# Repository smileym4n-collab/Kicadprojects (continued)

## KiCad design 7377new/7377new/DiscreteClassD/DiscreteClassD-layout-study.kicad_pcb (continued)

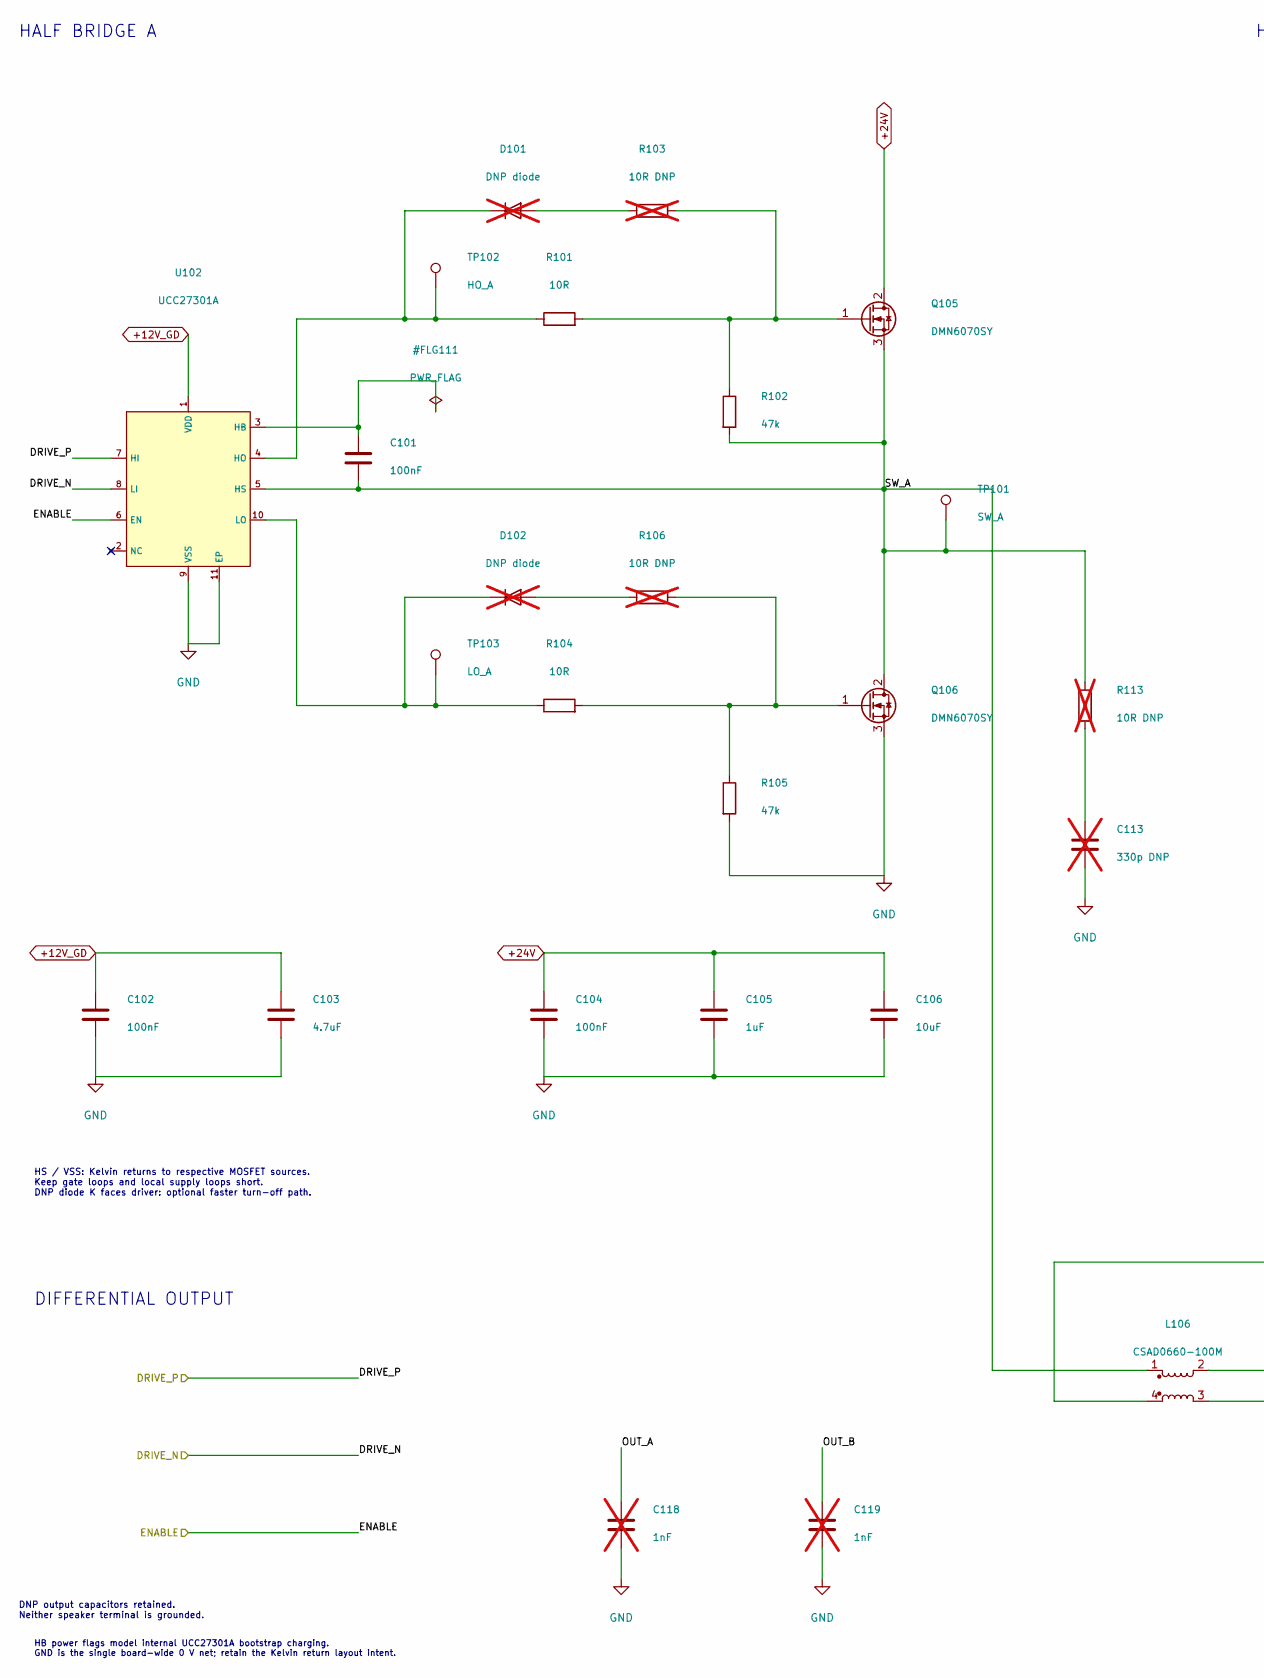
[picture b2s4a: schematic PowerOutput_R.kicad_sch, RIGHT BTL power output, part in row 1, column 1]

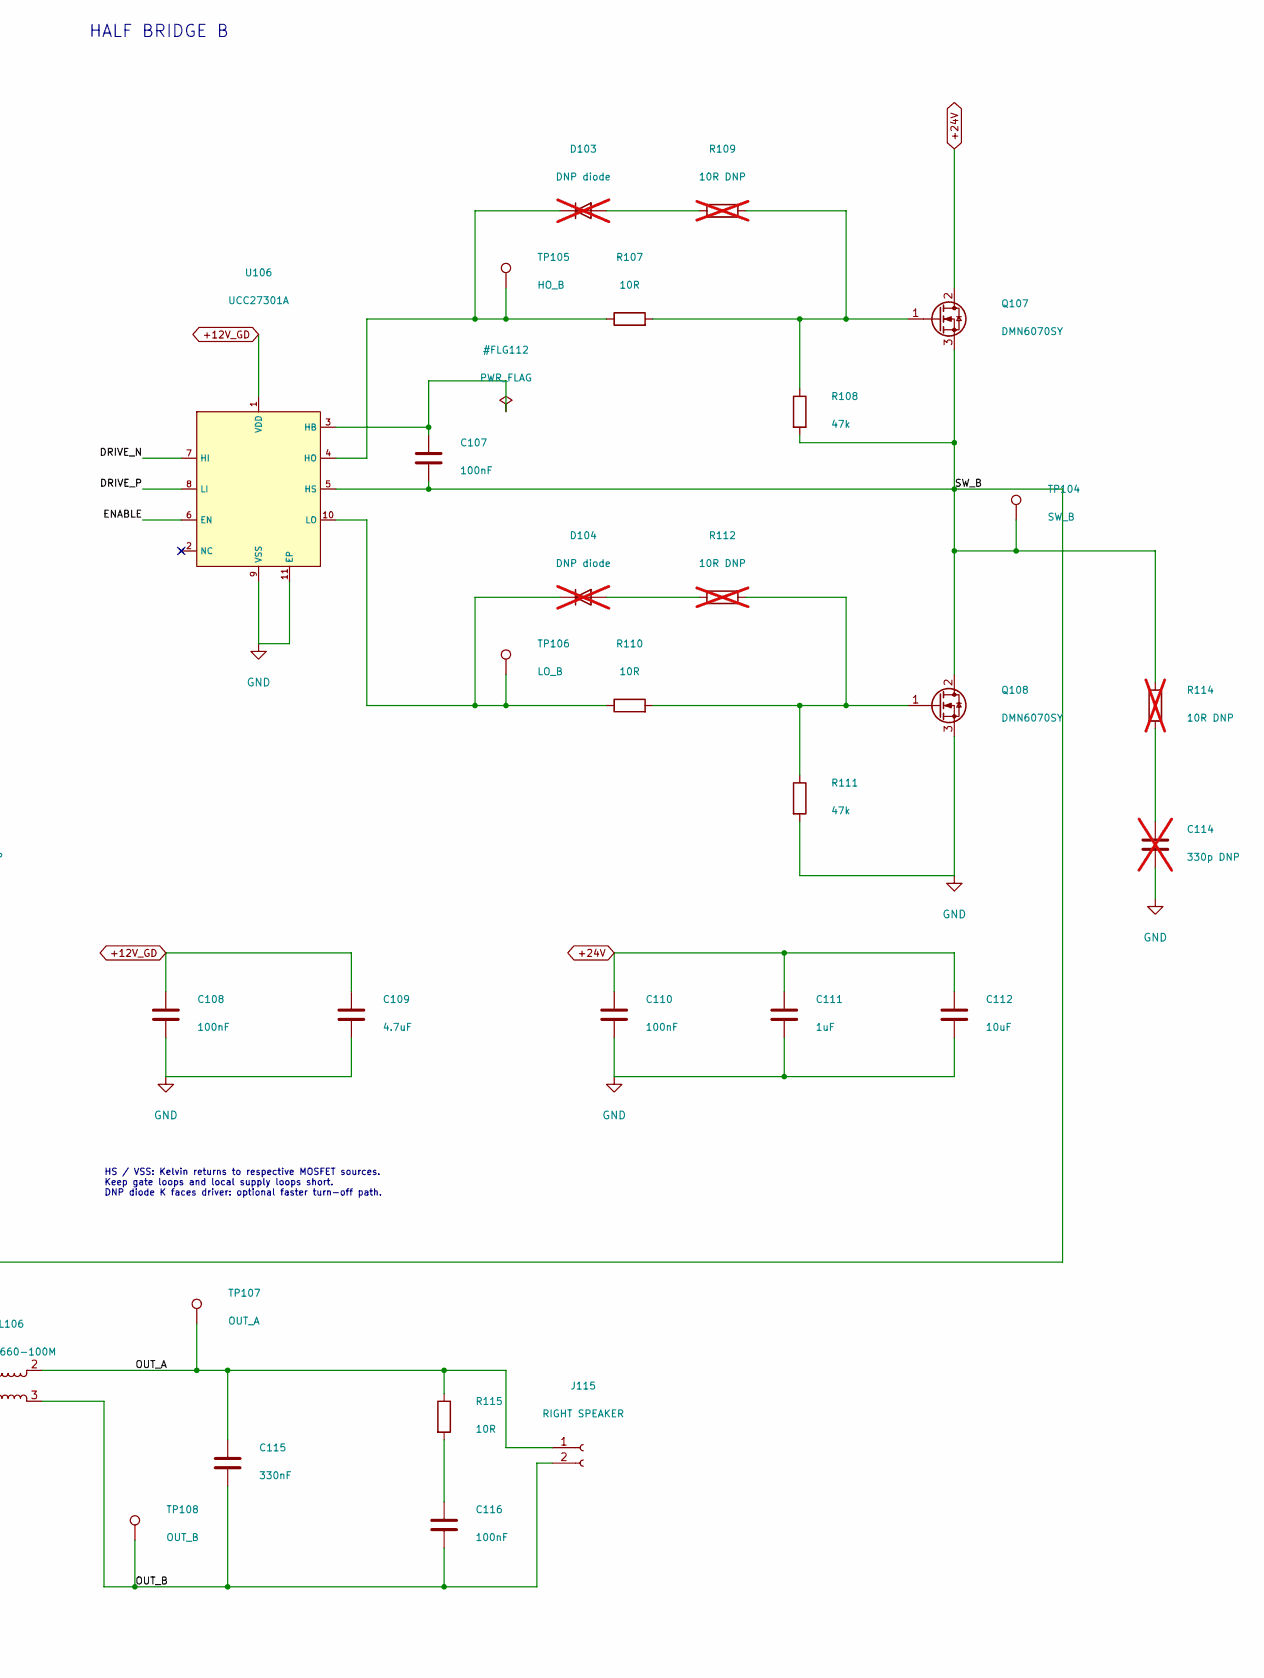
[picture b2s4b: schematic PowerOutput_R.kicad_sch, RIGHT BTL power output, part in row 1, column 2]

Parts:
C101, C102, C107, C108: 100nF; C_0805_2012Metric
C103, C109: 4.7uF; C_0805_2012Metric
C104, C110, C116: 100nF; C_1206_3216Metric_Pad1.33x1.80mm_HandSolder
C105, C111: 1uF; C_1206_3216Metric_Pad1.33x1.80mm_HandSolder
C106, C112: 10uF; C_1206_3216Metric_Pad1.33x1.80mm_HandSolder
C113, C114: 330p DNP; C_0805_2012Metric; Voltage 100V; not fitted
C115: 330nF; C_Rect_L7.2mm_W3.0mm_P5.00mm_FKS2_FKP2_MKS2_MKP2; Voltage 100V
C118, C119: 1nF; C_0805_2012Metric_Pad1.18x1.45mm_HandSolder; not fitted
D101, D102, D103, D104: DNP diode; D_SOD-123; not fitted
J115: RIGHT SPEAKER; Molex_KK-396_A-41791-0002_1x02_P3.96mm_Vertical
L106: CSAD0660-100M
Q105, Q106, Q107, Q108: DMN6070SY; SOT-89-3
R101, R104, R107, R110: 10R; R_0805_2012Metric
R102, R105, R108, R111: 47k; R_0805_2012Metric
R103, R106, R109, R112: 10R DNP; R_0805_2012Metric; not fitted
R113, R114: 10R DNP; R_1206_3216Metric; not fitted
R115: 10R; R_2512_6332Metric
TP101: SW_A; TestPoint_Pad_D1.5mm
TP102: HO_A; TestPoint_Pad_D1.5mm
TP103: LO_A; TestPoint_Pad_D1.5mm
TP104: SW_B; TestPoint_Pad_D1.5mm
TP105: HO_B; TestPoint_Pad_D1.5mm
TP106: LO_B; TestPoint_Pad_D1.5mm
TP107: OUT_A; TestPoint_Pad_D1.5mm
TP108: OUT_B; TestPoint_Pad_D1.5mm
U102, U106: UCC27301A; VSON-10-1EP_3x3mm_P0.5mm_EP1.65x2.4mm

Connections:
+12V_GD: C102.1, C103.1, C108.1, C109.1, U102.1 (VDD), U106.1 (VDD); also elsewhere on the board
+24V: C104.1, C105.1, C106.1, C110.1, C111.1, C112.1, Q105.2 (D), Q107.2 (D); also elsewhere on the board
/ENABLE_R: U102.6 (EN), U106.6 (EN); also elsewhere on the board
/RIGHT OUTPUT/OUT_A: C115.1, C118.1, J115.1, L106.2, R115.1, TP107.1 (1_1)
/RIGHT OUTPUT/OUT_B: C115.2, C116.2, C119.1, J115.2, L106.3, TP108.1 (1_1)
/RIGHT OUTPUT/SW_A: C101.2, L106.1, Q105.3 (S), Q106.2 (D), R102.2, R113.1, TP101.1 (1_1), U102.5 (HS)
/RIGHT OUTPUT/SW_B: C107.2, L106.4, Q107.3 (S), Q108.2 (D), R108.2, R114.1, TP104.1 (1_1), U106.5 (HS)
/R_DRIVE_N: U102.8 (LI), U106.7 (HI); also elsewhere on the board
/R_DRIVE_P: U102.7 (HI), U106.8 (LI); also elsewhere on the board
GND: C102.2, C103.2, C104.2, C105.2, C106.2, C108.2, C109.2, C110.2, C111.2, C112.2, C113.2, C114.2, C118.2, C119.2, Q106.3 (S), Q108.3 (S), R105.2, R111.2, U102.9 (VSS), U102.11 (EP), U106.9 (VSS), U106.11 (EP); also elsewhere on the board
unnamed: C113.1, R113.2
unnamed: C114.1, R114.2
unnamed: C116.1, R115.2
unnamed: D101.2 (A), R103.1
unnamed: D101.1 (K), R101.1, TP102.1 (1_1), U102.4 (HO)
unnamed: D102.2 (A), R106.1
unnamed: D102.1 (K), R104.1, TP103.1 (1_1), U102.10 (LO)
unnamed: D103.2 (A), R109.1
unnamed: D103.1 (K), R107.1, TP105.1 (1_1), U106.4 (HO)
unnamed: D104.2 (A), R112.1
unnamed: D104.1 (K), R110.1, TP106.1 (1_1), U106.10 (LO)
unnamed: Q105.1 (G), R101.2, R102.1, R103.2
unnamed: Q106.1 (G), R104.2, R105.1, R106.2
unnamed: Q107.1 (G), R107.2, R108.1, R109.2
unnamed: Q108.1 (G), R110.2, R111.1, R112.2
unnamed: C101.1, U102.3 (HB)
unnamed: C107.1, U106.3 (HB)

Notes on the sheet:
HS / VSS: Kelvin returns to respective MOSFET sources. Keep gate loops and local supply loops short. DNP diode K faces driver: optional faster turn-off path.
HB power flags model internal UCC27301A bootstrap charging. GND is the single board-wide 0 V net; retain the Kelvin return layout intent.
HALF BRIDGE B
DIFFERENTIAL OUTPUT
HALF BRIDGE A
DNP output capacitors retained. Neither speaker terminal is grounded.

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
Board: 4 copper layers, 195 parts (0 on the bottom side), 81 nets, no tracks yet.

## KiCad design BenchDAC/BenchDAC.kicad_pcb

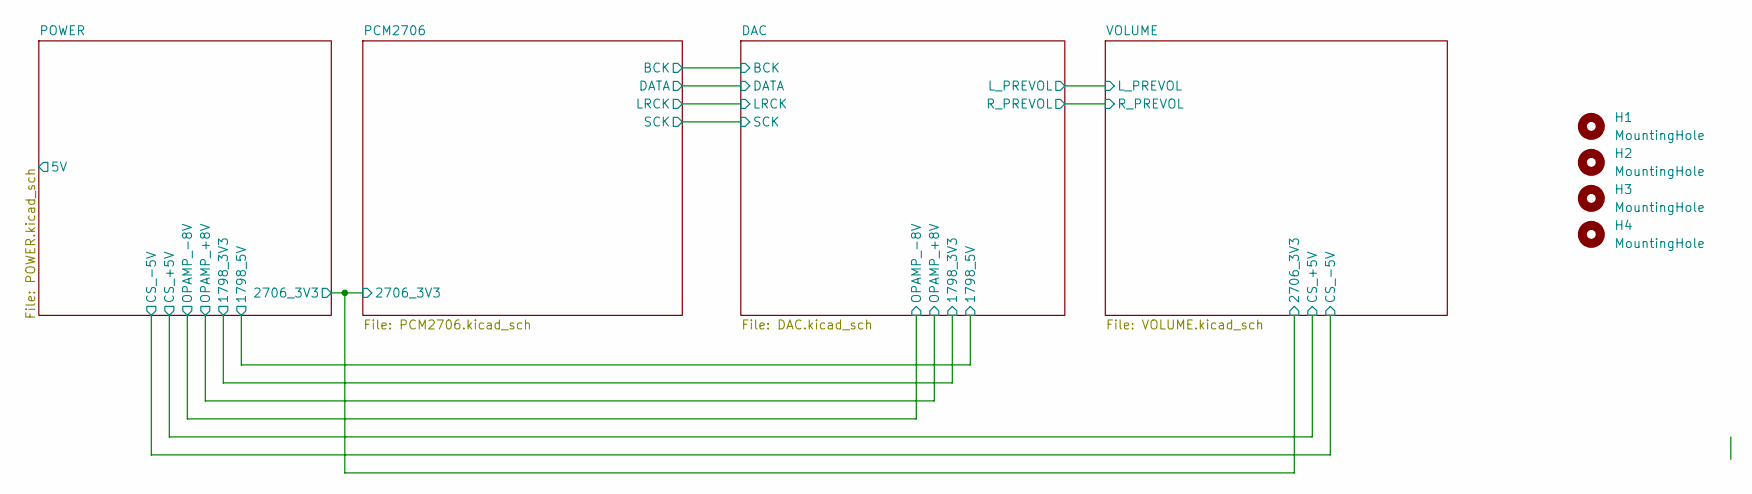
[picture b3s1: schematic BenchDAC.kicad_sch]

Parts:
H1, H2, H3, H4: MountingHole; MountingHole_3.2mm_M3

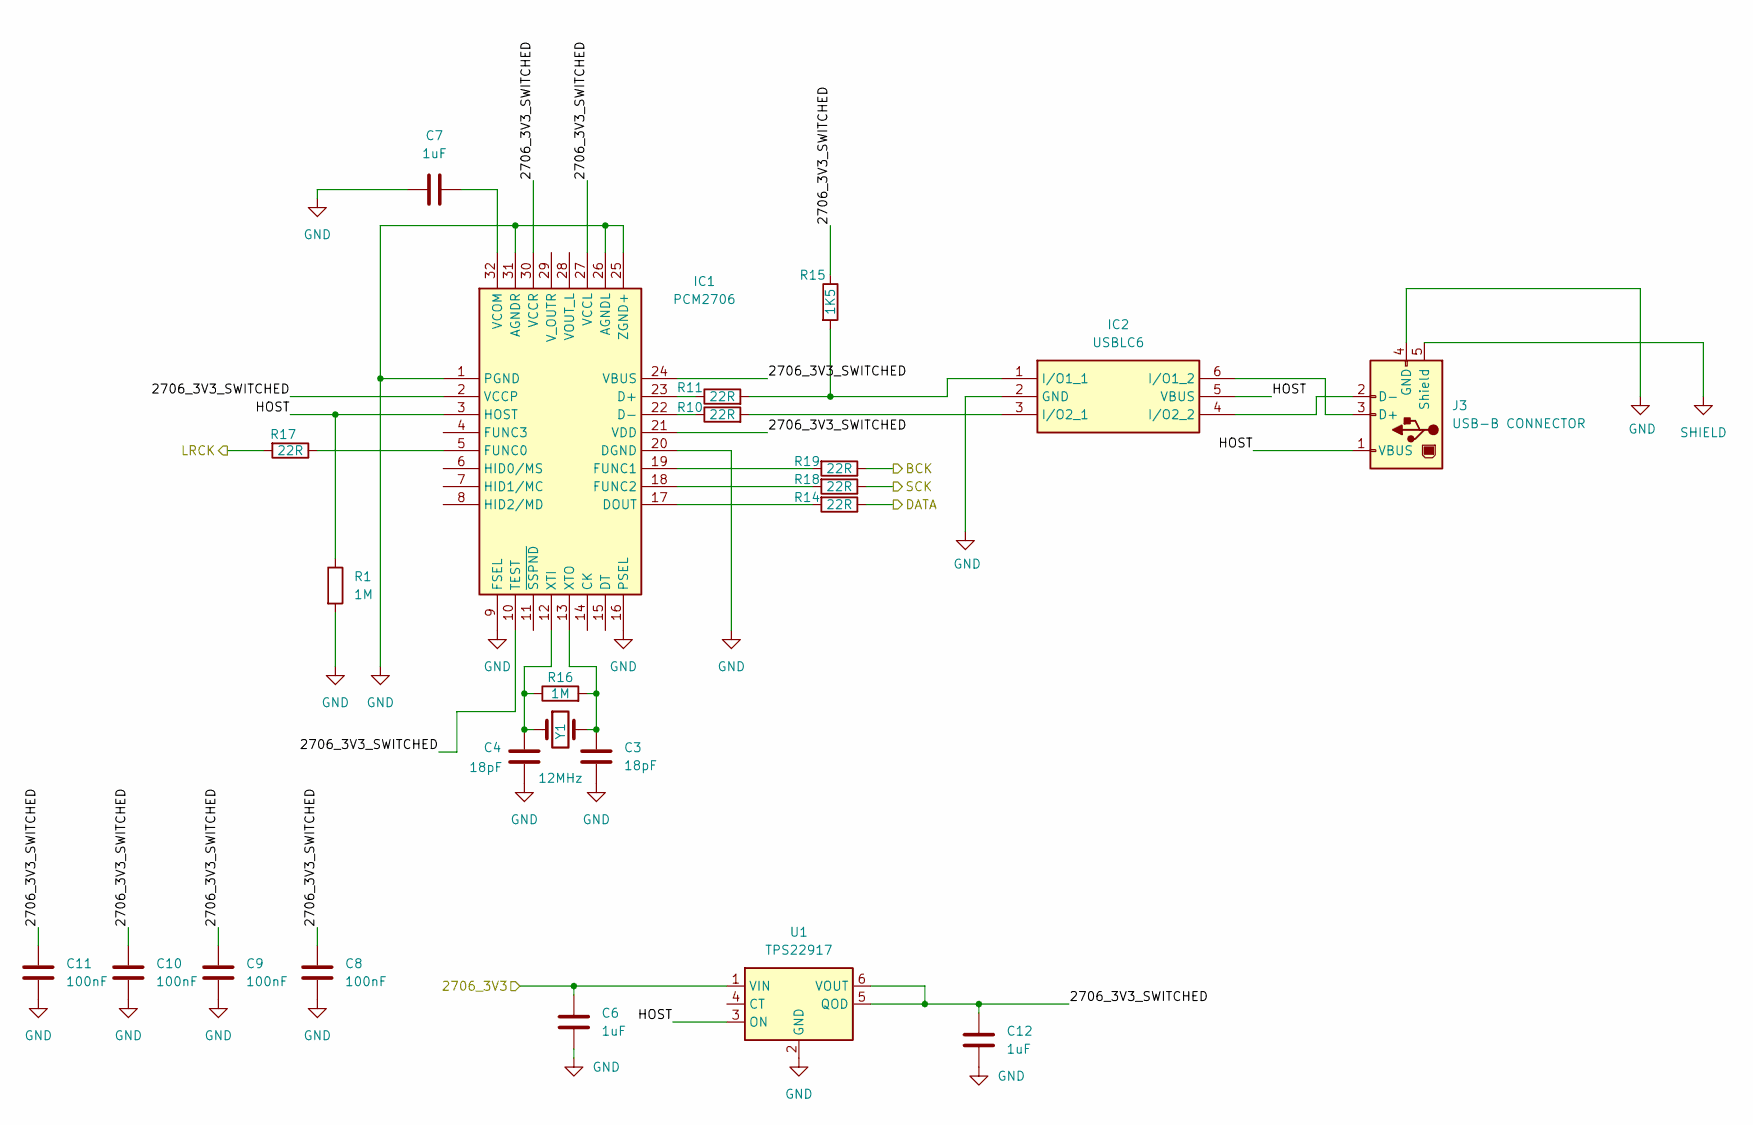
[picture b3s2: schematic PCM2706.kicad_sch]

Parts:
C3, C4: 18pF; C_0603_1608Metric_Pad1.08x0.95mm_HandSolder
C6, C7, C12: 1uF; C_1206_3216Metric_Pad1.33x1.80mm_HandSolder
C8, C9, C10, C11: 100nF; C_0603_1608Metric_Pad1.08x0.95mm_HandSolder
IC1: PCM2706; PCM2706C; Mouser Part Number 595-PCM2706CPJTR
IC2: USBLC6; SOT-23-6_Handsoldering; Mouser Part Number 511-USBLC6-2SC6
J3: USB-B CONNECTOR; USBC
R1, R16: 1M; R_0603_1608Metric_Pad0.98x0.95mm_HandSolder
R10, R11, R14, R17, R18, R19: 22R; R_0603_1608Metric_Pad0.98x0.95mm_HandSolder
R15: 1K5; R_0603_1608Metric_Pad0.98x0.95mm_HandSolder
U1: TPS22917; SOT-23-6
Y1: 12MHz; Crystal_HC49-U_Vertical

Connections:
/DAC/BCK: R19.1; also elsewhere on the board
/DAC/DATA: R14.1; also elsewhere on the board
/DAC/LRCK: R17.2; also elsewhere on the board
/DAC/SCK: R18.1; also elsewhere on the board
/PCM2706/2706_3V3: C6.1, U1.1 (VIN); also elsewhere on the board
/PCM2706/2706_3V3_SWITCHED: C8.1, C9.1, C10.1, C11.1, C12.1, IC1.2 (VCCP), IC1.10 (TEST), IC1.21 (VDD), IC1.24 (VBUS), IC1.27 (VCCL), IC1.30 (VCCR), R15.1, U1.5 (QOD), U1.6 (VOUT)
/PCM2706/HOST: IC1.3 (HOST), IC2.5 (VBUS), J3.1 (VBUS), R1.1, U1.3 (ON)
GND: C3.2, C4.2, C6.2, C7.1, C8.2, C9.2, C10.2, C11.2, C12.2, IC1.1 (PGND), IC1.9 (FSEL), IC1.16 (PSEL), IC1.20 (DGND), IC1.25 (ZGND+), IC1.26 (AGNDL), IC1.31 (AGNDR), IC2.2 (GND), J3.4 (GND), R1.2, U1.2 (GND); also elsewhere on the board
unnamed: IC1.23 (D+), R11.1
unnamed: IC1.22 (D-), R10.1
unnamed: IC1.17 (DOUT), R14.2
unnamed: IC1.5 (FUNC0), R17.1
unnamed: IC1.19 (FUNC1), R19.2
unnamed: IC1.18 (FUNC2), R18.2
unnamed: C7.2, IC1.32 (VCOM)
unnamed: C4.1, IC1.12 (XTI), R16.1, Y1.1
unnamed: C3.1, IC1.13 (XTO), R16.2, Y1.2
unnamed: IC2.1 (I/O1_1), R11.2, R15.2
unnamed: IC2.6 (I/O1_2), J3.3 (D+)
unnamed: IC2.3 (I/O2_1), R10.2
unnamed: IC2.4 (I/O2_2), J3.2 (D-)
SHIELD: J3.5 (Shield)

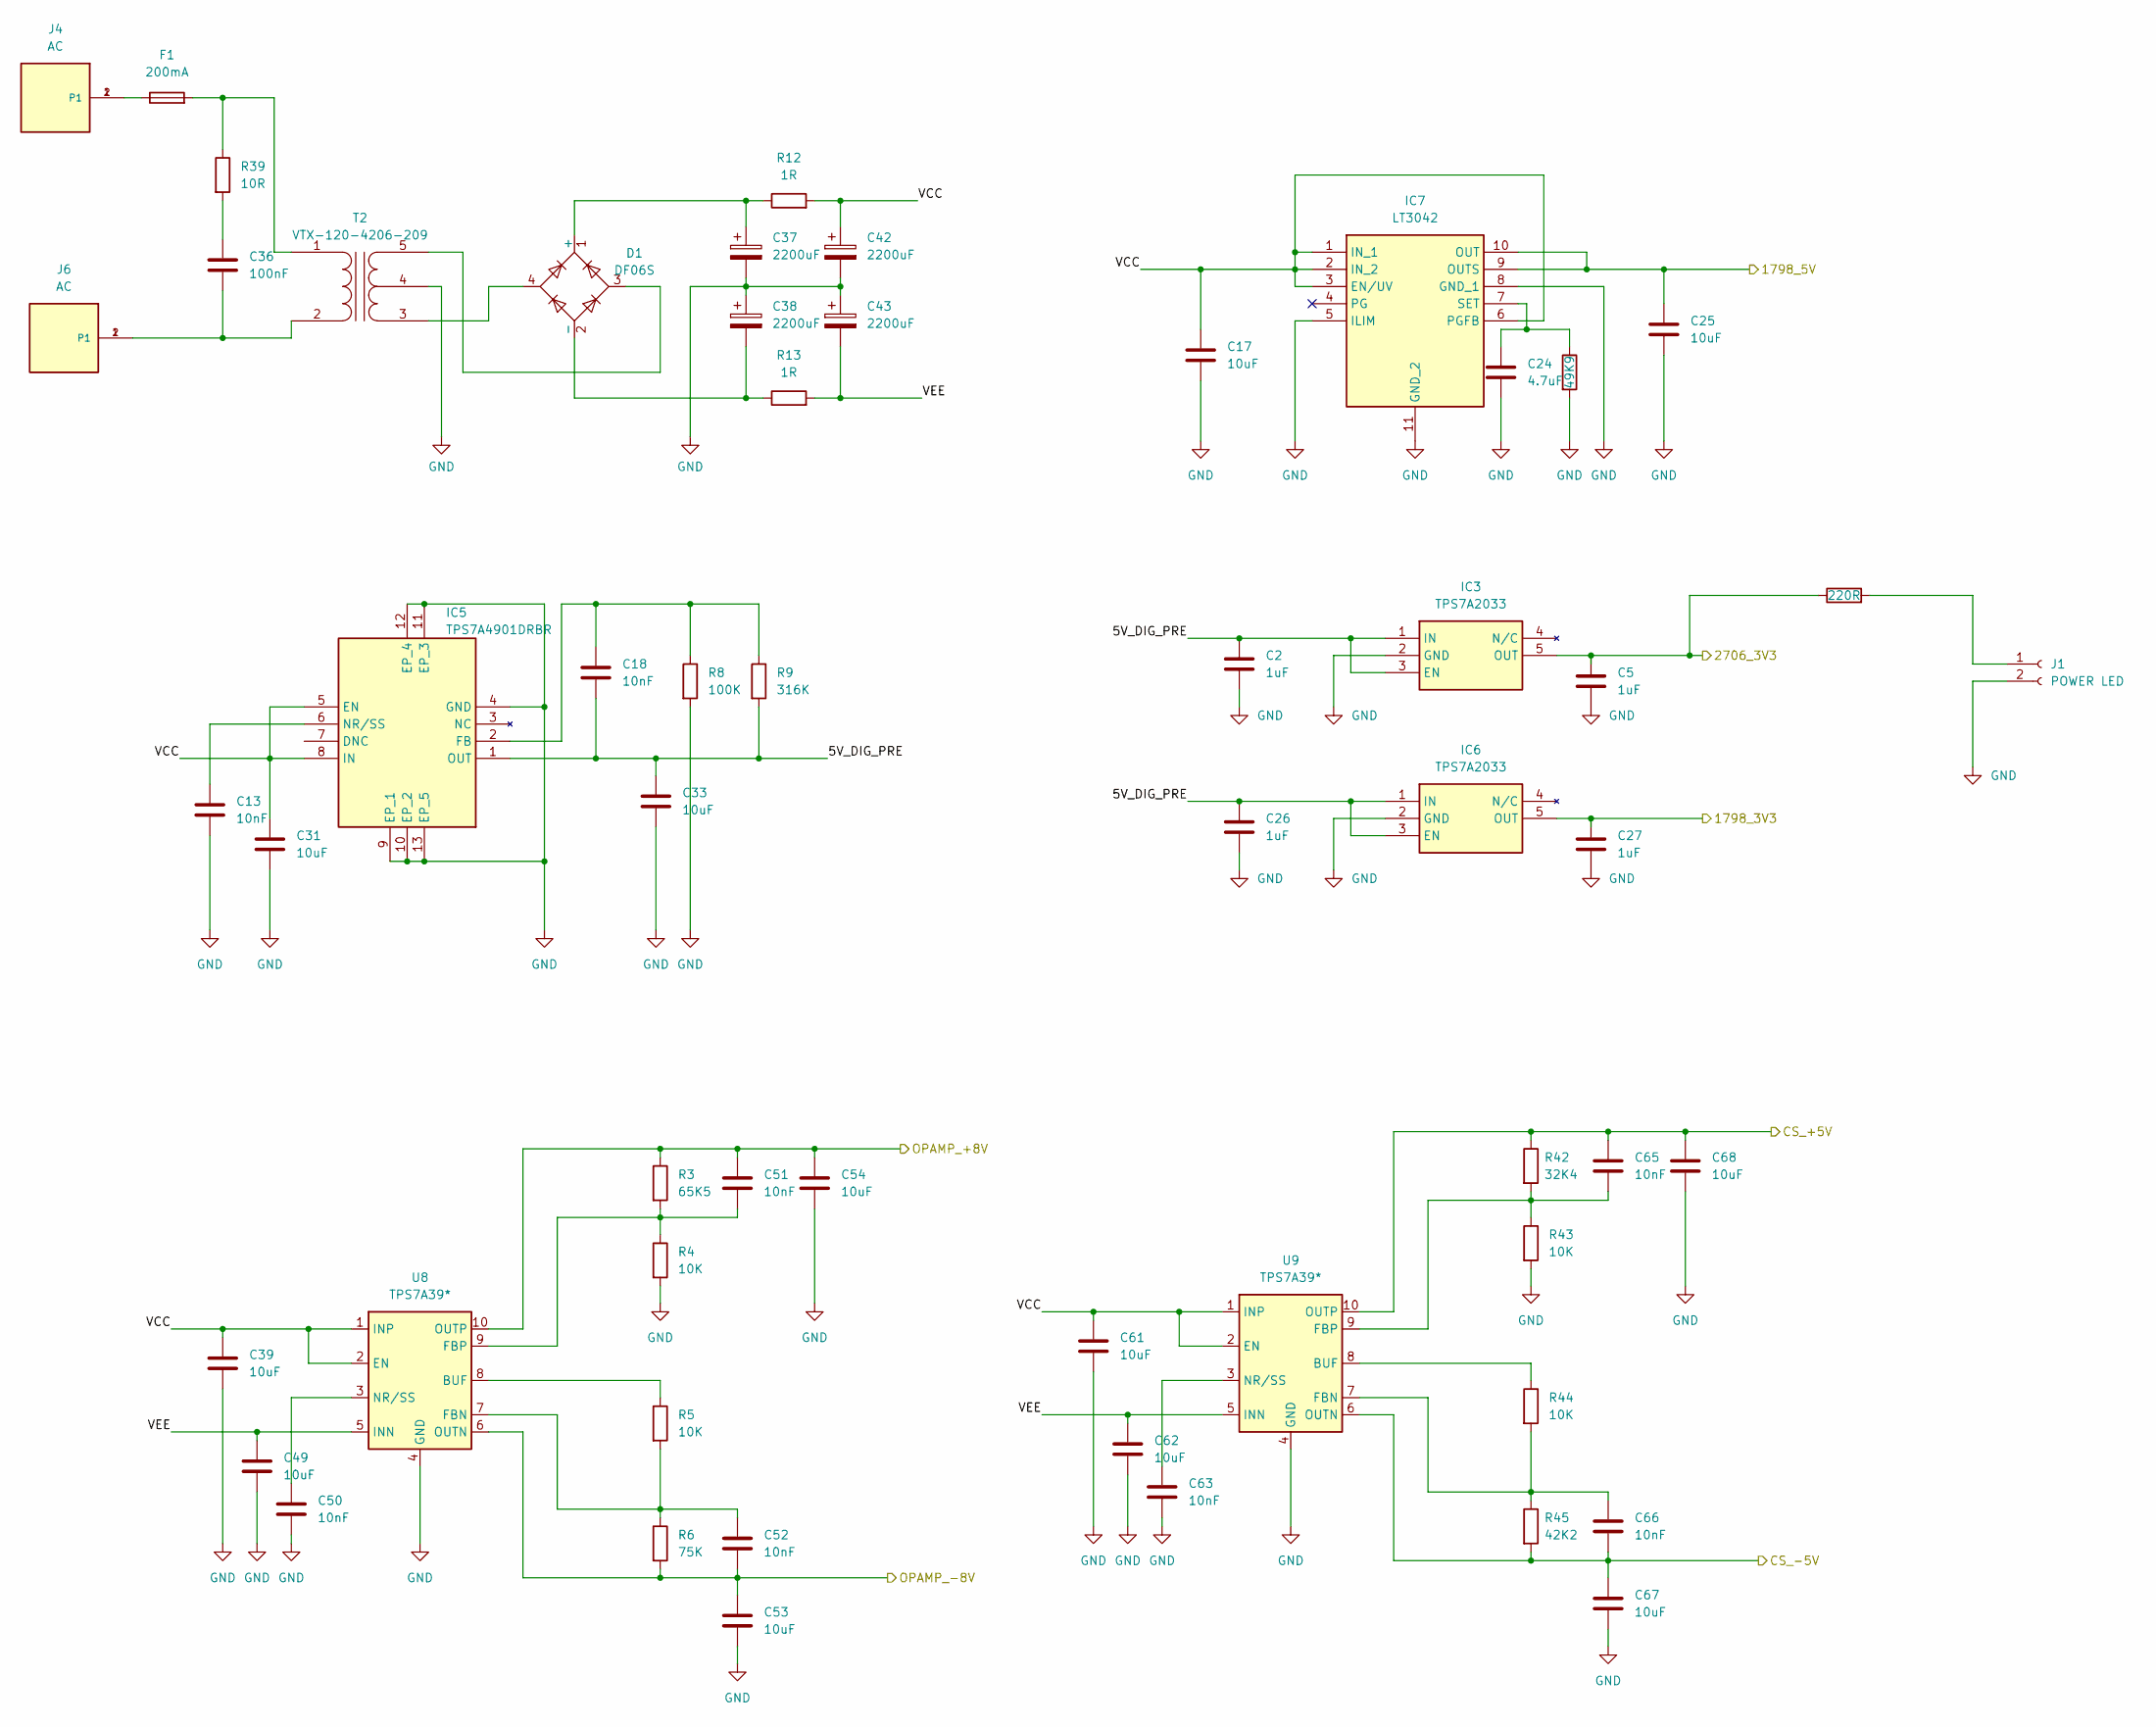
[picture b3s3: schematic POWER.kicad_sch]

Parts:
C2, C5, C26, C27: 1uF; C_1206_3216Metric_Pad1.33x1.80mm_HandSolder
C13, C18, C50, C51, C52, C63, C65, C66: 10nF; C_0805_2012Metric_Pad1.18x1.45mm_HandSolder
C17: 10uF; C_1206_3216Metric_Pad1.33x1.80mm_HandSolder; Manufacturer_Part_Number CL21A106KOQNNNF
C24: 4.7uF; C_0805_2012Metric_Pad1.18x1.45mm_HandSolder; Manufacturer_Part_Number CL21A475KAQNNNE
C25: 10uF; C_1206_3216Metric_Pad1.33x1.80mm_HandSolder; Manufacturer_Part_Number TMK316B7106KL-TD
C31, C33, C39, C49, C53, C54, C61, C62, C67, C68: 10uF; C_1206_3216Metric_Pad1.33x1.80mm_HandSolder
C36: 100nF; C_Rect_L18.0mm_W5.0mm_P15.00mm_FKS3_FKP3
C37, C38, C42, C43: 2200uF; CP_Radial_D16.0mm_P7.50mm
D1: DF06S; Diode_Bridge_OnSemi_SDIP-4L
F1: 200mA; Fuseholder_Cylinder-5x20mm_Schurter_0031_8201_Horizontal_Op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
IC3, IC6: TPS7A2033; SOT95P280X145-5N; Mouser Part Number 595-TPS7A2033PDBVR
IC5: TPS7A4901DRBR; Mouser Part Number 595-TPS7A4901DRBR
IC7: LT3042; Manufacturer_Part_Number LT3042EDD; LCSC Part # C666563
J1: POWER LED; JST_XH_B2B-XH-A_1x02_P2.50mm_Vertical
J4, J6: AC; TE_62409-1; PART_DESCRIPTION CONN QC TAB 0.250 SOLDER
R2: 49K9; R_0805_2012Metric_Pad1.20x1.40mm_HandSolder; Manufacturer_Part_Number 49K9ThinFilm
R3: 65K5; R_0805_2012Metric_Pad1.20x1.40mm_HandSolder
R4, R5, R43, R44: 10K; R_0805_2012Metric_Pad1.20x1.40mm_HandSolder
R6: 75K; R_0805_2012Metric_Pad1.20x1.40mm_HandSolder
R8: 100K; R_0805_2012Metric_Pad1.20x1.40mm_HandSolder
R9: 316K; R_0805_2012Metric_Pad1.20x1.40mm_HandSolder
R12, R13: 1R; R_Axial_DIN0414_L11.9mm_D4.5mm_P15.24mm_Horizontal
R39: 10R; R_Axial_DIN0617_L17.0mm_D6.0mm_P20.32mm_Horizontal
R42: 32K4; R_0805_2012Metric_Pad1.20x1.40mm_HandSolder
R45: 42K2; R_0805_2012Metric_Pad1.20x1.40mm_HandSolder
R46: 220R; R_0805_2012Metric_Pad1.20x1.40mm_HandSolder; Manufacturer_Part_Number 49K9ThinFilm
T2: VTX-120-4206-209; VTX Transformers
U8, U9: TPS7A39*; Texas_S-PVSON-N10_ThermalVias

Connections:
/DAC/1798_3V3: C27.1, IC6.5 (OUT); also elsewhere on the board
/DAC/1798_5V: C25.1, IC7.9 (OUTS), IC7.10 (OUT); also elsewhere on the board
/DAC/OPAMP_+8V: C51.1, C54.1, R3.1, U8.10 (OUTP); also elsewhere on the board
/DAC/OPAMP_-8V: C52.2, C53.1, R6.2, U8.6 (OUTN); also elsewhere on the board
/PCM2706/2706_3V3: C5.1, IC3.5 (OUT), R46.1; also elsewhere on the board
/POWER/5V_DIG_PRE: C2.1, C18.2, C26.1, C33.2, IC3.1 (IN), IC3.3 (EN), IC5.1 (OUT), IC6.1 (IN), IC6.3 (EN), R9.2
/POWER/CS_+5V: C65.1, C68.1, R42.1, U9.10 (OUTP); also elsewhere on the board
/POWER/CS_-5V: C66.2, C67.1, R45.2, U9.6 (OUTN); also elsewhere on the board
/POWER/VCC: C17.2, C31.2, C39.1, C42.1, C61.1, IC5.5 (EN), IC5.8 (IN), IC7.1 (IN_1), IC7.2 (IN_2), IC7.3 (EN/UV), IC7.6 (PGFB), R12.2, U8.1 (INP), U8.2 (EN), U9.1 (INP), U9.2 (EN)
/POWER/VEE: C43.2, C49.1, C62.1, R13.2, U8.5 (INN), U9.5 (INN)
GND: C2.2, C5.2, C13.2, C17.1, C24.2, C25.2, C26.2, C27.2, C31.1, C33.1, C37.2, C38.1, C39.2, C42.2, C43.1, C49.2, C50.2, C53.2, C54.2, C61.2, C62.2, C63.2, C67.2, C68.2, IC3.2 (GND), IC5.4 (GND), IC5.9 (EP_1), IC5.10 (EP_2), IC5.11 (EP_3), IC5.12 (EP_4), IC5.13 (EP_5), IC6.2 (GND), IC7.5 (ILIM), IC7.8 (GND_1), IC7.11 (GND_2), J1.2, R2.2, R4.2, R8.2, R43.2, T2.4 (SC), U8.4 (GND), U8.11 (GND), U9.4 (GND), U9.11 (GND); also elsewhere on the board
unnamed: C36.1, R39.2
unnamed: C37.1, D1.1 (+), R12.1
unnamed: C38.2, D1.2 (-), R13.1
unnamed: F1.1, J4.1, J4.2 (P1)
unnamed: C18.1, IC5.2 (FB), R8.1, R9.1
unnamed: C13.1, IC5.6 (NR/SS)
unnamed: C24.1, IC7.7 (SET), R2.1
unnamed: J1.1, R46.2
unnamed: F1.2, R39.1, T2.1 (AA)
unnamed: C36.2, J6.1, J6.2 (P1), T2.2 (AB)
unnamed: D1.4, T2.3 (SA)
unnamed: D1.3, T2.5 (SB)
unnamed: R5.1, U8.8 (BUF)
unnamed: C52.1, R5.2, R6.1, U8.7 (FBN)
unnamed: C51.2, R3.2, R4.1, U8.9 (FBP)
unnamed: C50.1, U8.3 (NR/SS)
unnamed: R44.1, U9.8 (BUF)
unnamed: C66.1, R44.2, R45.1, U9.7 (FBN)
unnamed: C65.2, R42.2, R43.1, U9.9 (FBP)
unnamed: C63.1, U9.3 (NR/SS)

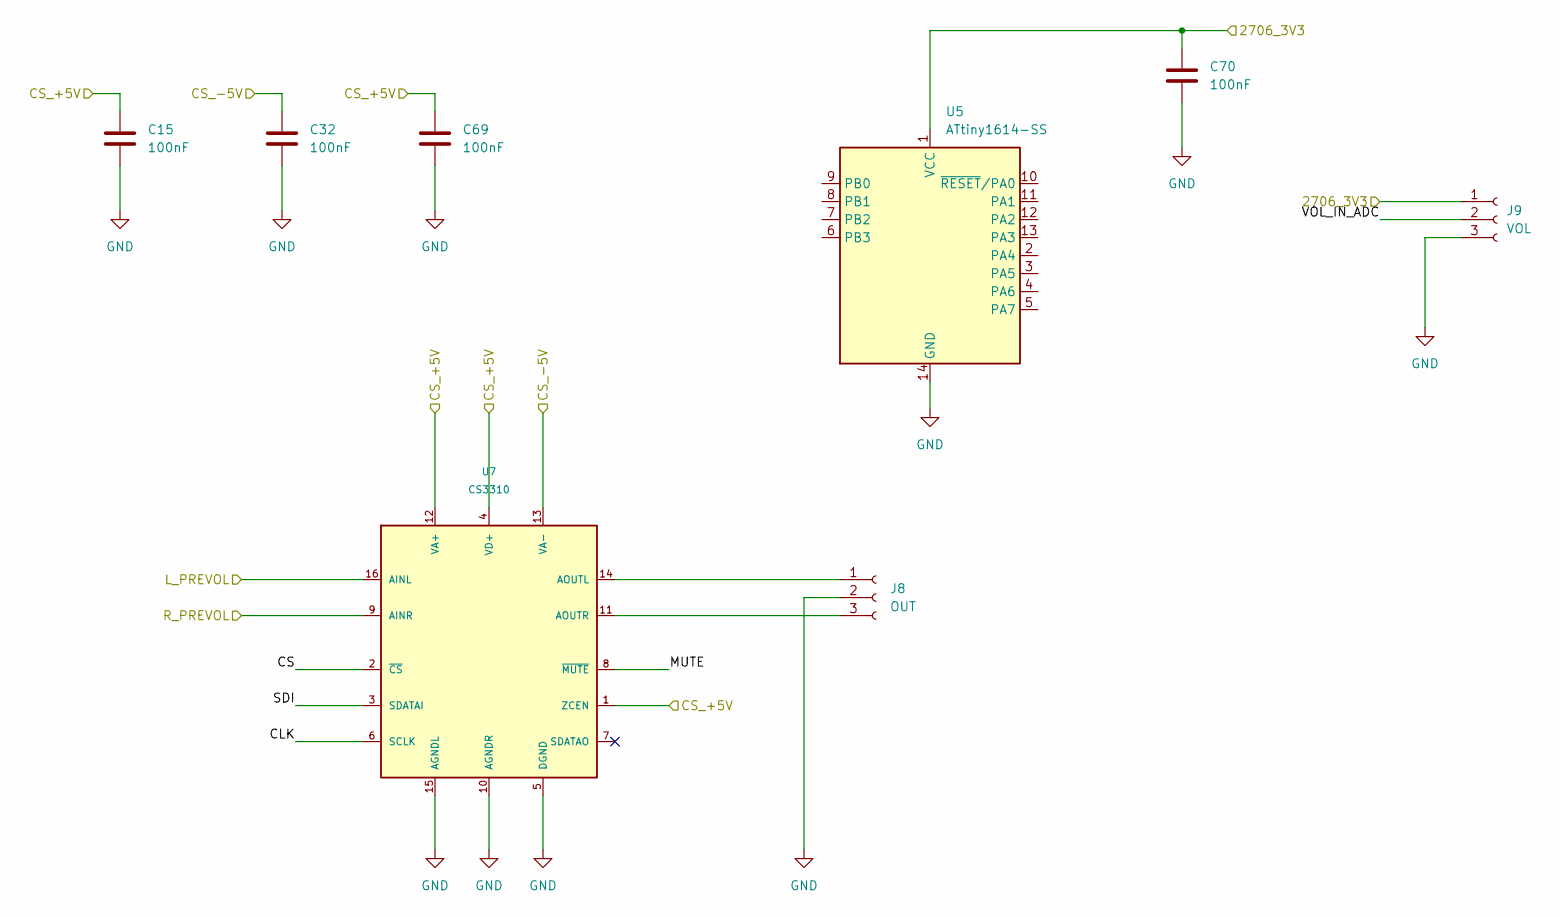
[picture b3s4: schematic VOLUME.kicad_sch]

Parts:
C15, C32, C69, C70: 100nF; C_0603_1608Metric_Pad1.08x0.95mm_HandSolder
J8: OUT; JST_XH_B3B-XH-A_1x03_P2.50mm_Vertical
J9: VOL; JST_XH_B3B-XH-A_1x03_P2.50mm_Vertical
U5: ATtiny1614-SS; SOIC-14_3.9x8.7mm_P1.27mm
U7: CS3310; SOIC-16W_7.5x10.3mm_P1.27mm

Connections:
/DAC/L_PREVOL: U7.16 (AINL); also elsewhere on the board
/DAC/R_PREVOL: U7.9 (AINR); also elsewhere on the board
/PCM2706/2706_3V3: C70.1, J9.1, U5.1 (VCC); also elsewhere on the board
/POWER/CS_+5V: C15.1, C69.1, U7.1 (ZCEN), U7.4 (VD+), U7.12 (VA+); also elsewhere on the board
/POWER/CS_-5V: C32.1, U7.13 (VA-); also elsewhere on the board
/VOLUME/CLK: U7.6 (SCLK)
/VOLUME/CS: U7.2 (~CS)
/VOLUME/MUTE: U7.8 (~MUTE)
/VOLUME/SDI: U7.3 (SDATAI)
/VOLUME/VOL_IN_ADC: J9.2
GND: C15.2, C32.2, C69.2, C70.2, J8.2, J9.3, U5.14 (GND), U7.5 (DGND), U7.10 (AGNDR), U7.15 (AGNDL); also elsewhere on the board
unnamed: J8.1, U7.14 (AOUTL)
unnamed: J8.3, U7.11 (AOUTR)
